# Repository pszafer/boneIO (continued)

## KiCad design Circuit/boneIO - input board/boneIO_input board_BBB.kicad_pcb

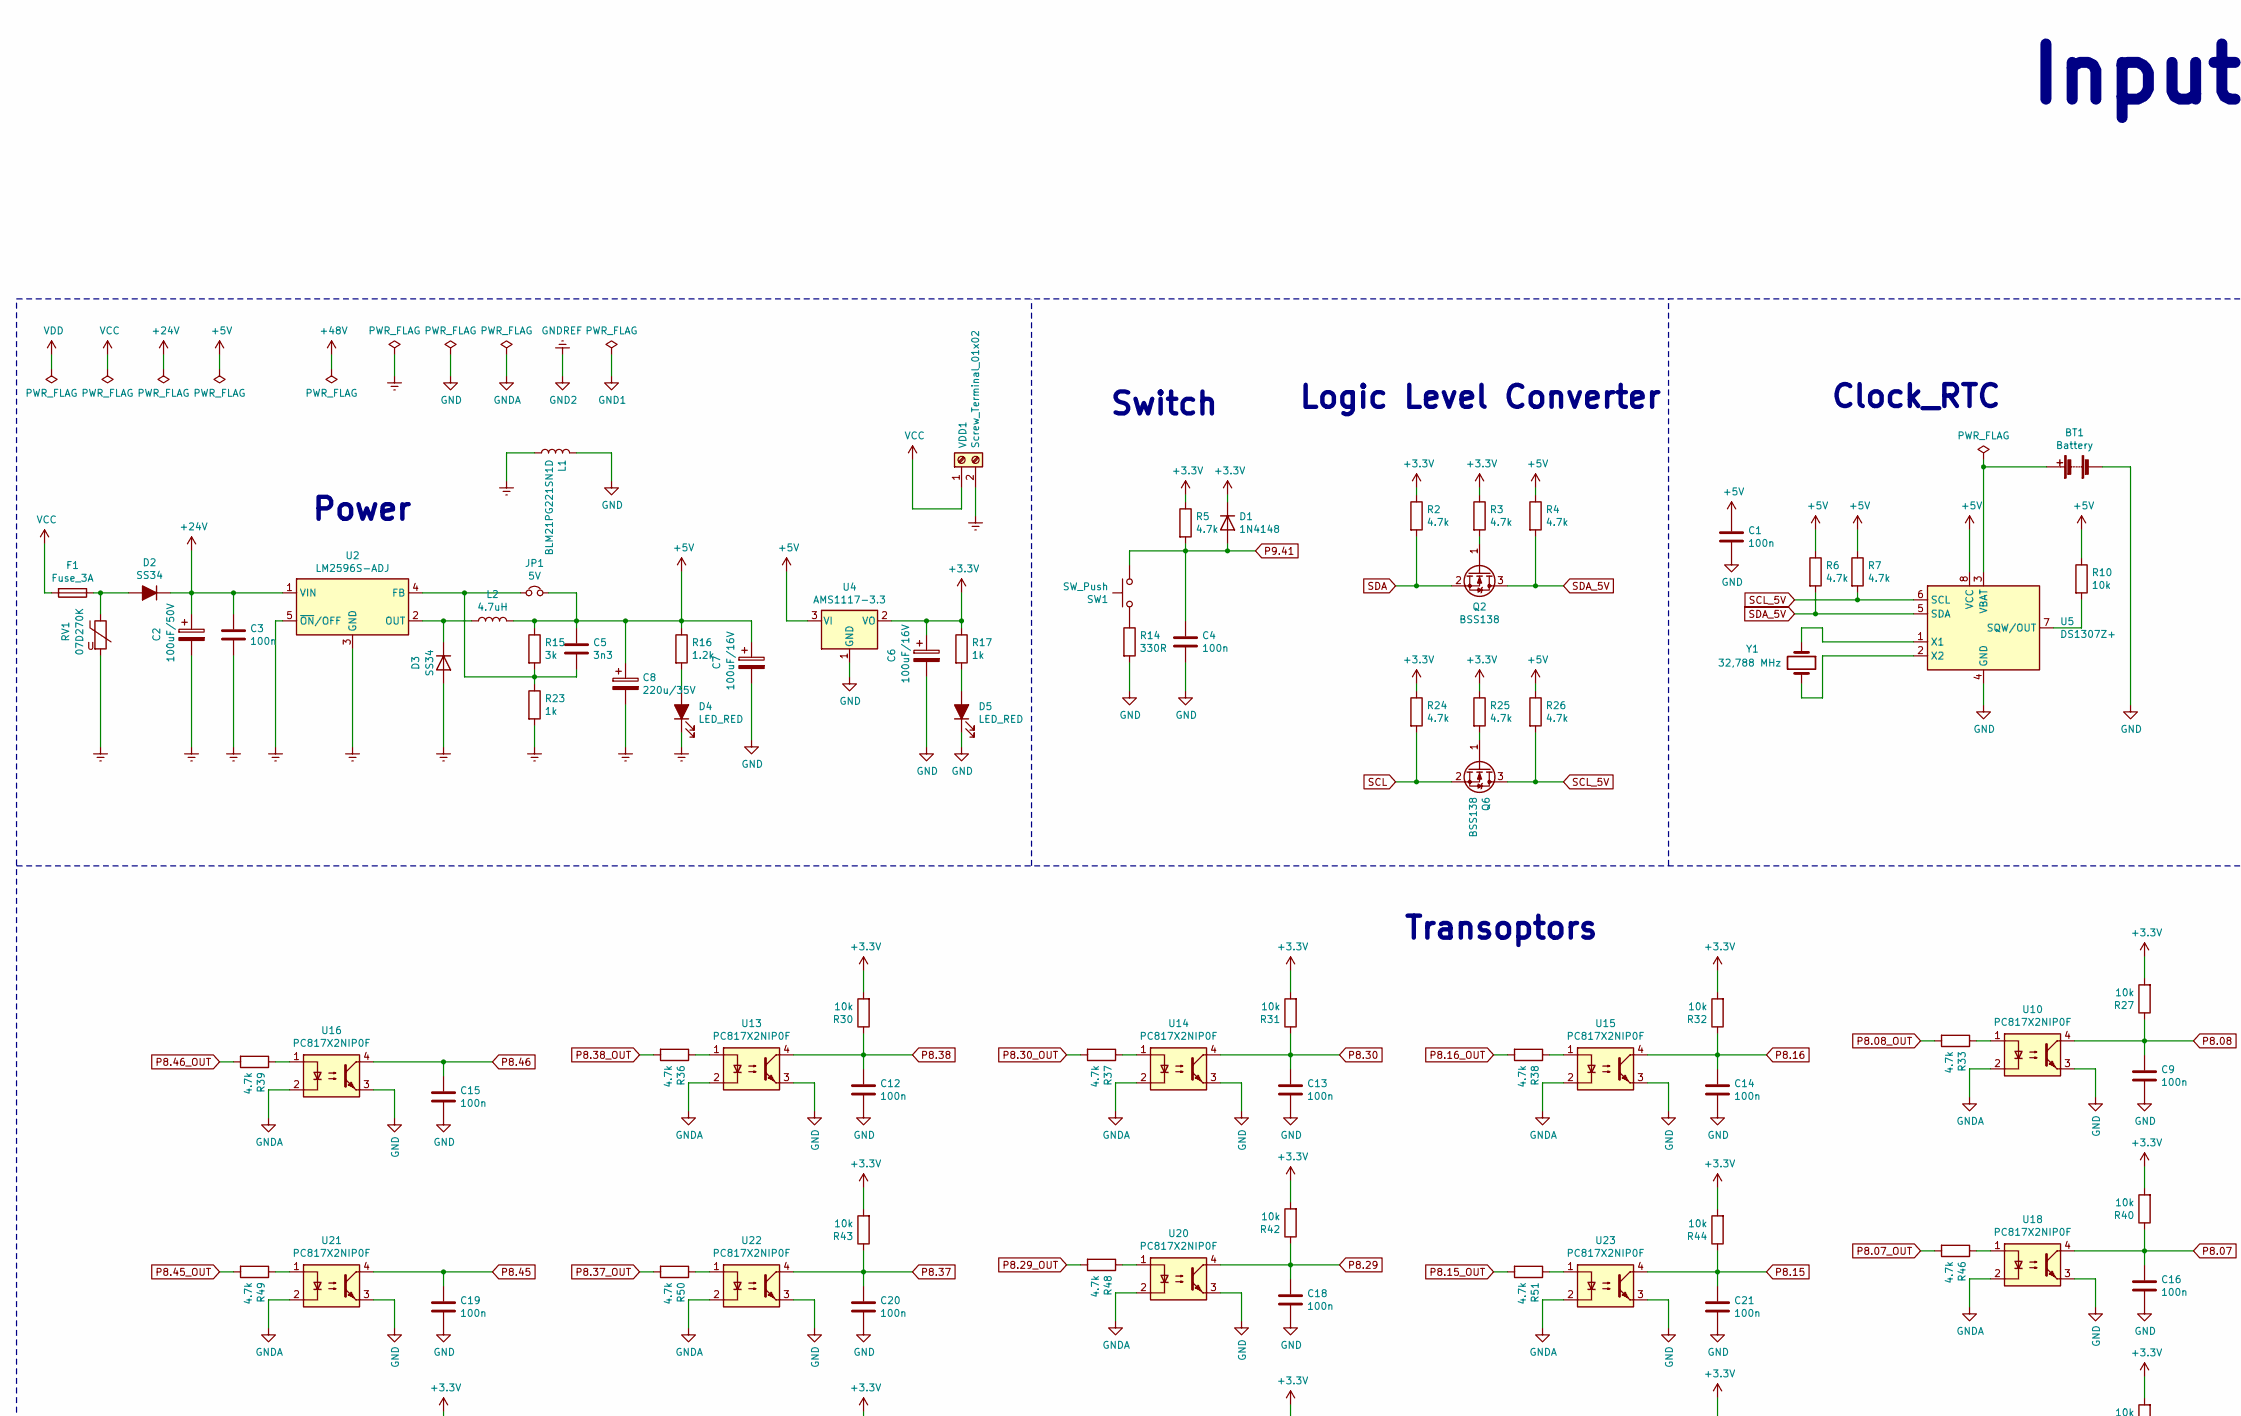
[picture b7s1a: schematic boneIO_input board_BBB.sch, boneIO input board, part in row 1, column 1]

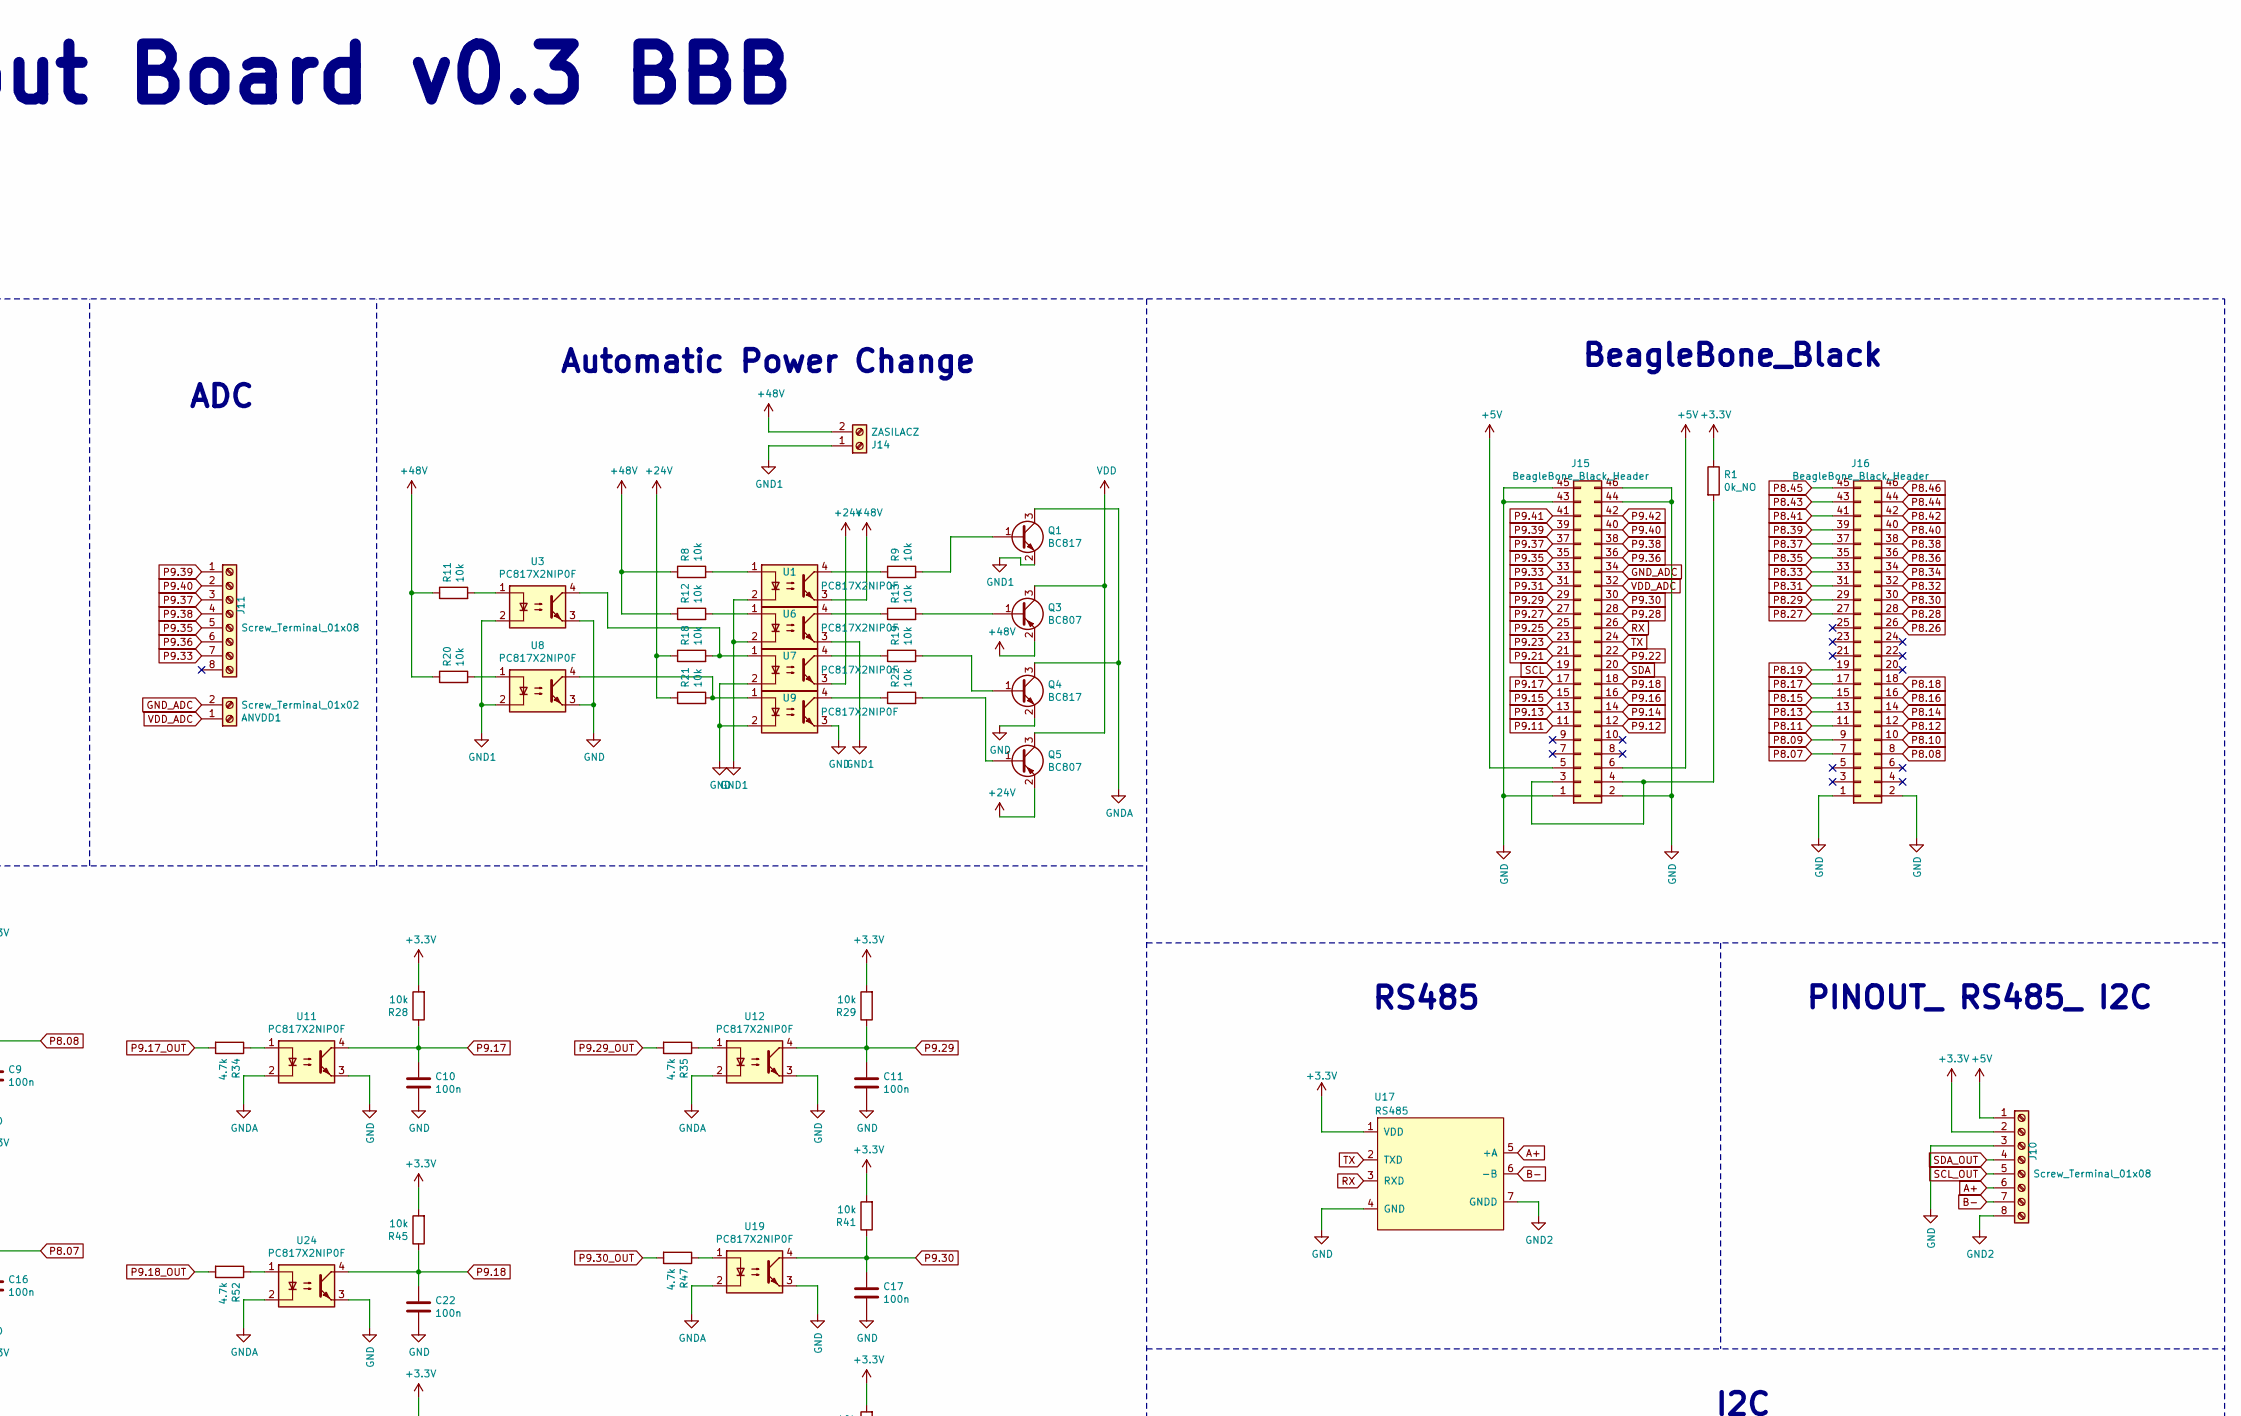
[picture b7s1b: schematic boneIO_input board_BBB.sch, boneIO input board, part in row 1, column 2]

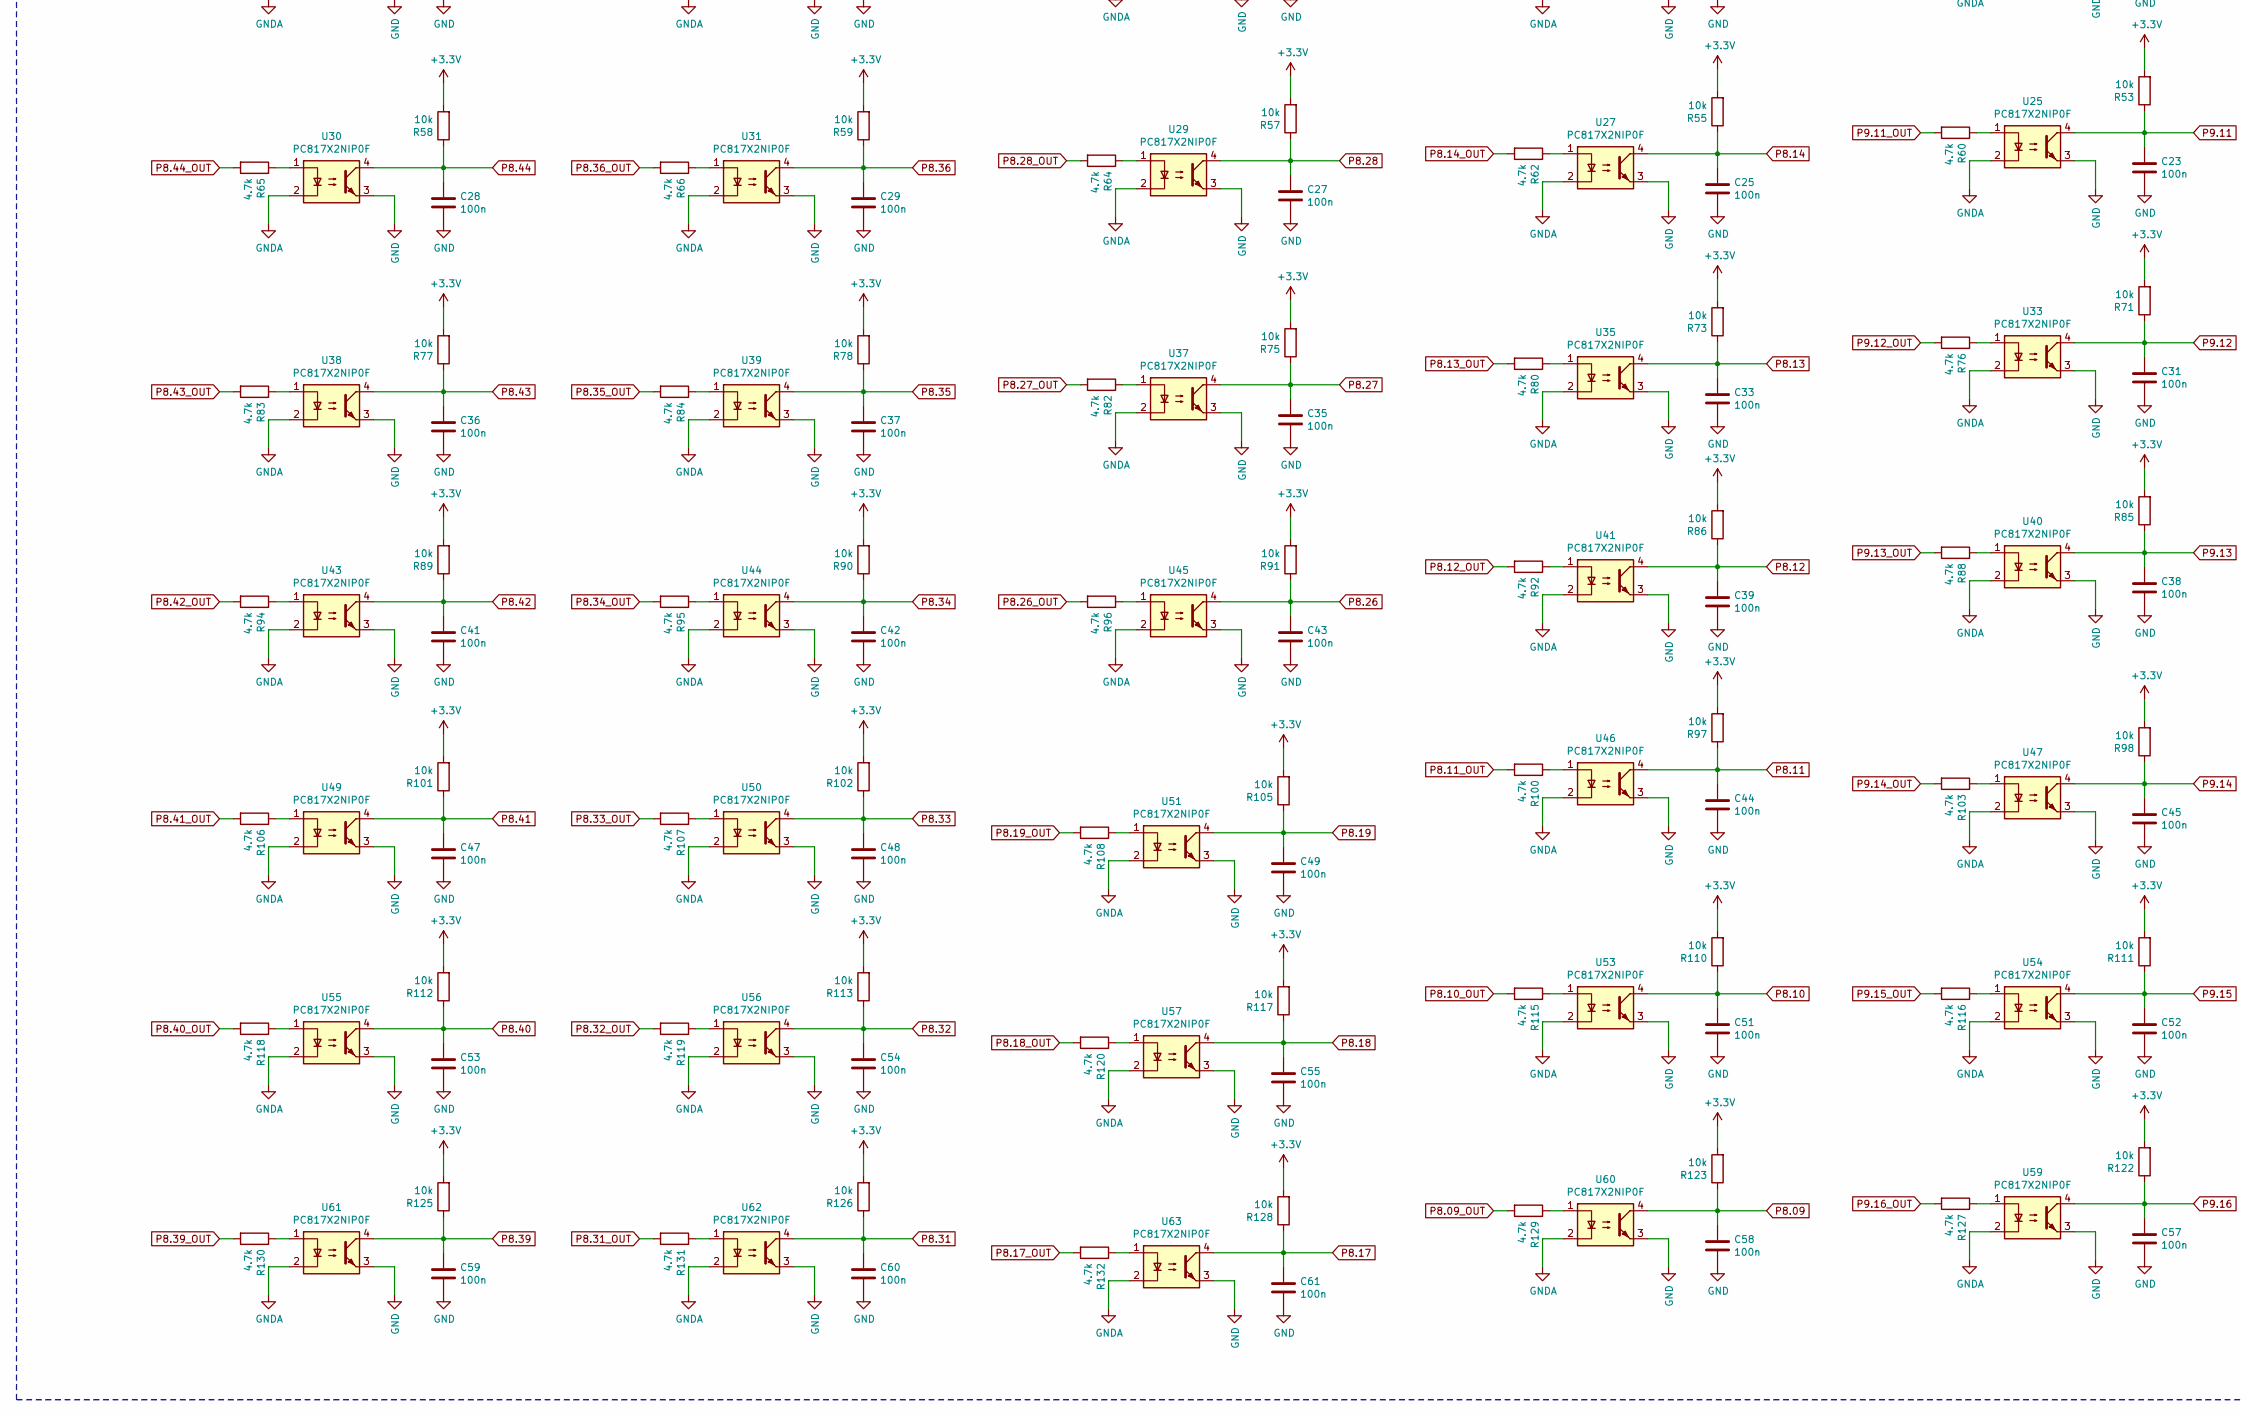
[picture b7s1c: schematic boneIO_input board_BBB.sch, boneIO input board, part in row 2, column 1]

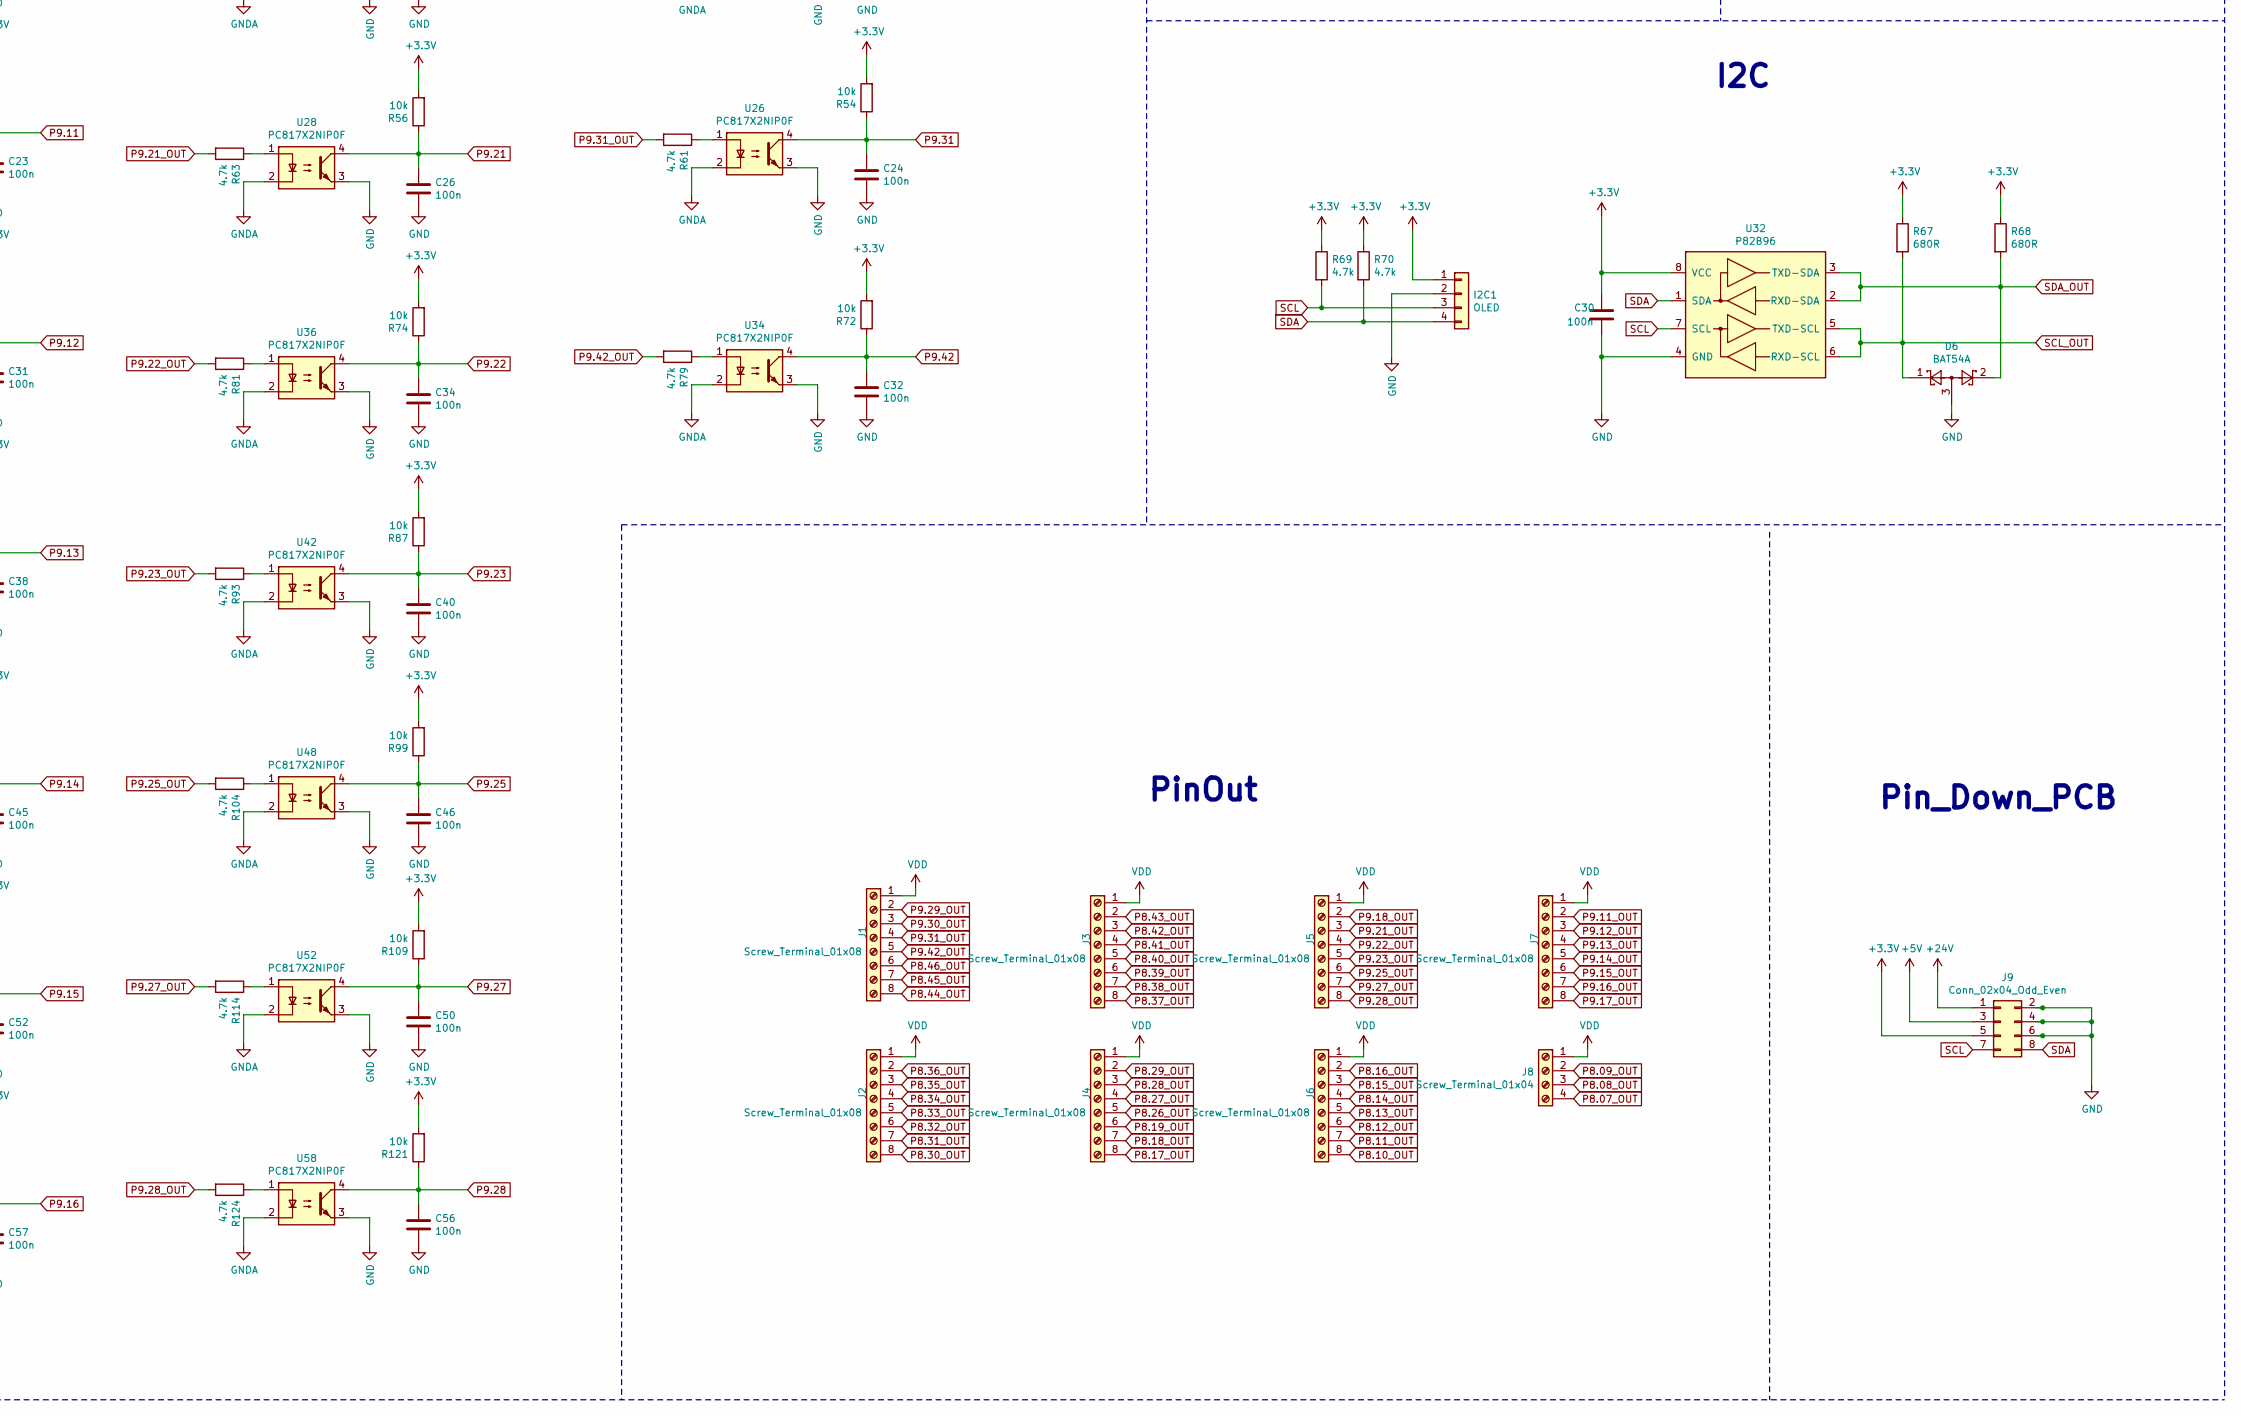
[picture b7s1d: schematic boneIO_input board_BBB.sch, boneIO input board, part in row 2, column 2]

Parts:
ANVDD1: Screw_Terminal_01x02; Phoenix_1x02_P5.00mm_Horizontal
BT1: Battery; Battery_Panasonic_CR1220-VCN_Vertical_CircularHoles
C1, C3, C4, C9, C10, C11, C12, C13, C14, C15, C16, C17, C18, C19, C20, C21, C22, C23, C24, C25, C26, C27, C28, C29, C30, C31, C32, C33, C34, C35, C36, C37, C38, C39, C40, C41, C42, C43, C44, C45, C46, C47, C48, C49, C50, C51, C52, C53, C54, C55, C56, C57, C58, C59, C60, C61: 100n; C_0603_1608Metric; JLCPCB C14663
C2: 100uF/50V; CP_Elec_8x10; JLCPCB C72480
C5: 3n3; C_0805_2012Metric; JLCPCB C107149
C6, C7: 100uF/16V; CP_Elec_6.3x5.4; JLCPCB C72480
C8: 220u/35V; CP_Elec_8x10; JLCPCB C311611
D1: 1N4148; D_MiniMELF; JLCPCB C68883
D2: SS34; D_SMA; JLCPCB C64982
D3: SS34; D_SMA; JLCPCB C8678
D4, D5: LED_RED; LED_0805_2012Metric; JLCPCB C84256
D6: BAT54A; SOT-23
F1: Fuse_3A; Fuse_2512_6332Metric; JLCPCB C136367
I2C1: OLED; PinSocket_1x04_P2.54mm_Vertical
J1, J2, J3, J4, J5, J6, J7, J10, J11: Screw_Terminal_01x08; 8pin
J8: Screw_Terminal_01x04; Phoenix_1x04_P5.00mm_Horizontal
J9: Conn_02x04_Odd_Even; PinSocket_2x04_P2.54mm_Vertical
J14: ZASILACZ; PhoenixContact_MSTBA_2,5_2-G_1x02_P5.00mm_Horizontal
J15, J16: BeagleBone_Black_Header; PinHeader_2x23_P2.54mm_Vertical
JP1: 5V; SolderJumper-2_P1.3mm_Open_Pad1.0x1.5mm
L1: BLM21PG221SN1D; L_0805_2012Metric; JLCPCB C85840
L2: 4.7uH; L_12x12mm_H6mm; JLCPCB C338848
Q1, Q4: BC817; SOT-23
Q2, Q6: BSS138; SOT-23
Q3, Q5: BC807; SOT-23
R1: 0k_NO; R_0805_2012Metric; JLCPCB C238881
R2, R3, R4, R6, R7, R24, R25, R26: 4.7k; R_0603_1608Metric; JLCPCB C238881
R5, R33, R34, R35, R36, R37, R38, R39, R46, R47, R48, R49, R50, R51, R52, R60, R61, R62, R63, R64, R65, R66, R69, R70, R76, R79, R80, R81, R82, R83, R84, R88, R92, R93, R94, R95, R96, R100, R103, R104, R106, R107, R108, R114, R115, R116, R118, R119, R120, R124, R127, R129, R130, R131, R132: 4.7k; R_0603_1608Metric; JLCPCB C237118
R8, R9, R10, R11, R12, R13, R18, R19, R20, R21, R22, R27, R28, R29, R30, R31, R32, R40, R41, R42, R43, R44, R45, R53, R54, R55, R56, R57, R58, R59, R71, R72, R73, R74, R75, R77, R78, R85, R86, R87, R89, R90, R91, R97, R98, R99, R101, R102, R105, R109, R110, R111, R112, R113, R117, R121, R122, R123, R125, R126, R128: 10k; R_0603_1608Metric; JLCPCB C238881
R14: 330R; R_0603_1608Metric; JLCPCB C101062
R15: 3k; R_0603_1608Metric; JLCPCB C126358
R16: 1.2k; R_0603_1608Metric; JLCPCB C269704
R17, R23: 1k; R_0603_1608Metric; JLCPCB C269704
R67, R68: 680R; R_0603_1608Metric; JLCPCB C269704
RV1: 07D270K; RV_Disc_D7mm_W3.5mm_P5mm; JLCPCB C317745
SW1: SW_Push; SW_PUSH_6mm_H13mm
U1, U3, U6, U7, U8, U9, U10, U11, U12, U13, U14, U15, U16, U18, U19, U20, U21, U22, U23, U24, U25, U26, U27, U28, U29, U30, U31, U33, U34, U35, U36, U37, U38, U39, U40, U41, U42, U43, U44, U45, U46, U47, U48, U49, U50, U51, U52, U53, U54, U55, U56, U57, U58, U59, U60, U61, U62, U63: PC817X2NIP0F; SOT254P975X400-4N; JLCPCB C6649
U2: LM2596S-ADJ; TO-263-5_TabPin3
U4: AMS1117-3.3; SOT-223-3_TabPin2
U5: DS1307Z+; SOIC-8_3.9x4.9mm_P1.27mm; JLCPCB C26858
U17: RS485; RS485_moduleTTL
U32: P82B96; SO-8_3.9x4.9mm_P1.27mm; JLCPCB C32103
VDD1: Screw_Terminal_01x02; Phoenix_1x02_P5.00mm_Horizontal
Y1: 32,788 MHz; Crystal_C26-LF_D2.1mm_L6.5mm_Horizontal

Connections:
+3V3: C6.1, C30.1, D1.1 (K), I2C1.1, J9.5, J10.2, R1.1, R2.1, R3.1, R5.1, R17.1, R24.1, R25.1, R27.2, R28.2, R29.2, R30.2, R31.2, R32.2, R40.2, R41.2, R42.2, R43.2, R44.2, R45.2, R53.2, R54.2, R55.2, R56.2, R57.2, R58.2, R59.2, R67.1, R68.1, R69.1, R70.1, R71.2, R72.2, R73.2, R74.2, R75.2, R77.2, R78.2, R85.2, R86.2, R87.2, R89.2, R90.2, R91.2, R97.2, R98.2, R99.2, R101.2, R102.2, R105.2, R109.2, R110.2, R111.2, R112.2, R113.2, R117.2, R121.2, R122.2, R123.2, R125.2, R126.2, R128.2, U4.2 (VO), U17.1 (VDD), U32.8 (VCC)
+5V: C1.1, C5.1, C7.1, C8.1, J9.3, J10.1, J15.5, J15.6, JP1.2, L2.2, R4.1, R6.1, R7.1, R10.1, R15.1, R16.1, R26.1, U4.3 (VI), U5.8 (VCC)
+24V: C2.1, C3.1, D2.1 (K), J9.1, Q5.2 (E), R18.1, R21.1, U2.1 (VIN), U7.3
+48V: J14.2, Q3.2 (E), R8.1, R11.1, R12.1, R20.1, U1.3
A+: J10.6, U17.5 (+A)
B-: J10.7, U17.6 (-B)
Earth: C2.2, C3.2, C8.2, D3.2 (A), D4.1 (K), L1.1, R23.2, RV1.2, U2.3 (GND), U2.5 (~ON~/OFF), VDD1.2
GND: BT1.2 (-), C1.2, C4.2, C6.2, C7.2, C9.2, C10.2, C11.2, C12.2, C13.2, C14.2, C15.2, C16.2, C17.2, C18.2, C19.2, C20.2, C21.2, C22.2, C23.2, C24.2, C25.2, C26.2, C27.2, C28.2, C29.2, C30.2, C31.2, C32.2, C33.2, C34.2, C35.2, C36.2, C37.2, C38.2, C39.2, C40.2, C41.2, C42.2, C43.2, C44.2, C45.2, C46.2, C47.2, C48.2, C49.2, C50.2, C51.2, C52.2, C53.2, C54.2, C55.2, C56.2, C57.2, C58.2, C59.2, C60.2, C61.2, D5.1 (K), D6.3, I2C1.2, J9.2, J9.4, J9.6, J10.3, J15.1, J15.2, J15.43, J15.44, J15.45, J15.46, J16.1, J16.2, L1.2, Q4.2 (E), R14.2, U3.3, U4.1 (GND), U5.4 (GND), U7.2, U8.3, U9.2, U9.3, U10.3, U11.3, U12.3, U13.3, U14.3, U15.3, U16.3, U17.4 (GND), U18.3, U19.3, U20.3, U21.3, U22.3, U23.3, U24.3, U25.3, U26.3, U27.3, U28.3, U29.3, U30.3, U31.3, U32.4 (GND), U33.3, U34.3, U35.3, U36.3, U37.3, U38.3, U39.3, U40.3, U41.3, U42.3, U43.3, U44.3, U45.3, U46.3, U47.3, U48.3, U49.3, U50.3, U51.3, U52.3, U53.3, U54.3, U55.3, U56.3, U57.3, U58.3, U59.3, U60.3, U61.3, U62.3, U63.3
GND1: J14.1, Q1.2 (E), U1.2, U3.2, U6.2, U6.3, U8.2
GND2: J10.8, U17.7 (GNDD)
GNDA: Q1.3 (C), Q4.3 (C), U10.2, U11.2, U12.2, U13.2, U14.2, U15.2, U16.2, U18.2, U19.2, U20.2, U21.2, U22.2, U23.2, U24.2, U25.2, U26.2, U27.2, U28.2, U29.2, U30.2, U31.2, U33.2, U34.2, U35.2, U36.2, U37.2, U38.2, U39.2, U40.2, U41.2, U42.2, U43.2, U44.2, U45.2, U46.2, U47.2, U48.2, U49.2, U50.2, U51.2, U52.2, U53.2, U54.2, U55.2, U56.2, U57.2, U58.2, U59.2, U60.2, U61.2, U62.2, U63.2
GND_ADC: ANVDD1.2, J15.34
unnamed: BT1.1 (+), U5.3 (VBAT)
unnamed: C5.2, JP1.1, R15.2, R23.1, U2.4 (FB)
unnamed: D2.2 (A), F1.1, RV1.1
unnamed: D3.1 (K), L2.1, U2.2 (OUT)
unnamed: D4.2 (A), R16.2
unnamed: D5.2 (A), R17.2
unnamed: J15.3, J15.4, R1.2
unnamed: Q1.1 (B), R9.2
unnamed: Q2.1 (G), R3.2
unnamed: Q3.1 (B), R13.2
unnamed: Q4.1 (B), R19.2
unnamed: Q5.1 (B), R22.2
unnamed: Q6.1 (G), R25.2
unnamed: R8.2, U1.1
unnamed: R9.1, U1.4
unnamed: R10.2, U5.7 (SQW/OUT)
unnamed: R11.2, U3.1
unnamed: R12.2, U6.1
unnamed: R13.1, U6.4
unnamed: R14.1, SW1.1
unnamed: R18.2, U3.4, U7.1
unnamed: R19.1, U7.4
unnamed: R20.2, U8.1
unnamed: R21.2, U8.4, U9.1
unnamed: R22.1, U9.4
unnamed: R33.1, U10.1
unnamed: R34.1, U11.1
unnamed: R35.1, U12.1
unnamed: R36.1, U13.1
unnamed: R37.1, U14.1
unnamed: R38.1, U15.1
unnamed: R39.1, U16.1
unnamed: R46.1, U18.1
unnamed: R47.1, U19.1
unnamed: R48.1, U20.1
unnamed: R49.1, U21.1
unnamed: R50.1, U22.1
unnamed: R51.1, U23.1
unnamed: R52.1, U24.1
unnamed: R60.1, U25.1
unnamed: R61.1, U26.1
unnamed: R62.1, U27.1
unnamed: R63.1, U28.1
unnamed: R64.1, U29.1
unnamed: R65.1, U30.1
unnamed: R66.1, U31.1
unnamed: R76.1, U33.1
unnamed: R79.1, U34.1
unnamed: R80.1, U35.1
unnamed: R81.1, U36.1
unnamed: R82.1, U37.1
unnamed: R83.1, U38.1
unnamed: R84.1, U39.1
unnamed: R88.1, U40.1
unnamed: R92.1, U41.1
unnamed: R93.1, U42.1
unnamed: R94.1, U43.1
unnamed: R95.1, U44.1
unnamed: R96.1, U45.1
unnamed: R100.1, U46.1
unnamed: R103.1, U47.1
unnamed: R104.1, U48.1
unnamed: R106.1, U49.1
unnamed: R107.1, U50.1
unnamed: R108.1, U51.1
unnamed: R114.1, U52.1
unnamed: R115.1, U53.1
unnamed: R116.1, U54.1
unnamed: R118.1, U55.1
unnamed: R119.1, U56.1
unnamed: R120.1, U57.1
unnamed: R124.1, U58.1
unnamed: R127.1, U59.1
unnamed: R129.1, U60.1
unnamed: R130.1, U61.1
unnamed: R131.1, U62.1
unnamed: R132.1, U63.1
unnamed: U5.1 (X1), Y1.1
unnamed: U5.2 (X2), Y1.2
P8.07: C16.1, J16.7, R40.1, U18.4
P8.07_OUT: J8.4, R46.2
P8.08: C9.1, J16.8, R27.1, U10.4
P8.08_OUT: J8.3, R33.2
P8.09: C58.1, J16.9, R123.1, U60.4
P8.09_OUT: J8.2, R129.2
P8.10: C51.1, J16.10, R110.1, U53.4
P8.10_OUT: J6.8, R115.2
P8.11: C44.1, J16.11, R97.1, U46.4
P8.11_OUT: J6.7, R100.2
P8.12: C39.1, J16.12, R86.1, U41.4
P8.12_OUT: J6.6, R92.2
P8.13: C33.1, J16.13, R73.1, U35.4
P8.13_OUT: J6.5, R80.2
P8.14: C25.1, J16.14, R55.1, U27.4
P8.14_OUT: J6.4, R62.2
P8.15: C21.1, J16.15, R44.1, U23.4
P8.15_OUT: J6.3, R51.2
P8.16: C14.1, J16.16, R32.1, U15.4
P8.16_OUT: J6.2, R38.2
P8.17: C61.1, J16.17, R128.1, U63.4
P8.17_OUT: J4.8, R132.2
P8.18: C55.1, J16.18, R117.1, U57.4
P8.18_OUT: J4.7, R120.2
P8.19: C49.1, J16.19, R105.1, U51.4
P8.19_OUT: J4.6, R108.2
P8.26: C43.1, J16.26, R91.1, U45.4
P8.26_OUT: J4.5, R96.2
P8.27: C35.1, J16.27, R75.1, U37.4
P8.27_OUT: J4.4, R82.2
P8.28: C27.1, J16.28, R57.1, U29.4
P8.28_OUT: J4.3, R64.2
P8.29: C18.1, J16.29, R42.1, U20.4
P8.29_OUT: J4.2, R48.2
P8.30: C13.1, J16.30, R31.1, U14.4
P8.30_OUT: J2.8, R37.2
P8.31: C60.1, J16.31, R126.1, U62.4
P8.31_OUT: J2.7, R131.2
P8.32: C54.1, J16.32, R113.1, U56.4
P8.32_OUT: J2.6, R119.2
P8.33: C48.1, J16.33, R102.1, U50.4
P8.33_OUT: J2.5, R107.2
P8.34: C42.1, J16.34, R90.1, U44.4
P8.34_OUT: J2.4, R95.2
P8.35: C37.1, J16.35, R78.1, U39.4
P8.35_OUT: J2.3, R84.2
P8.36: C29.1, J16.36, R59.1, U31.4
P8.36_OUT: J2.2, R66.2
P8.37: C20.1, J16.37, R43.1, U22.4
P8.37_OUT: J3.8, R50.2
P8.38: C12.1, J16.38, R30.1, U13.4
P8.38_OUT: J3.7, R36.2
P8.39: C59.1, J16.39, R125.1, U61.4
P8.39_OUT: J3.6, R130.2
P8.40: C53.1, J16.40, R112.1, U55.4
P8.40_OUT: J3.5, R118.2
P8.41: C47.1, J16.41, R101.1, U49.4
P8.41_OUT: J3.4, R106.2
P8.42: C41.1, J16.42, R89.1, U43.4
P8.42_OUT: J3.3, R94.2
P8.43: C36.1, J16.43, R77.1, U38.4
P8.43_OUT: J3.2, R83.2
P8.44: C28.1, J16.44, R58.1, U30.4
P8.44_OUT: J1.8, R65.2
P8.45: C19.1, J16.45, U21.4
P8.45_OUT: J1.7, R49.2
P8.46: C15.1, J16.46, U16.4
P8.46_OUT: J1.6, R39.2
P9.11: C23.1, J15.11, R53.1, U25.4
P9.11_OUT: J7.2, R60.2
P9.12: C31.1, J15.12, R71.1, U33.4
P9.12_OUT: J7.3, R76.2
P9.13: C38.1, J15.13, R85.1, U40.4
P9.13_OUT: J7.4, R88.2
P9.14: C45.1, J15.14, R98.1, U47.4
P9.14_OUT: J7.5, R103.2
P9.15: C52.1, J15.15, R111.1, U54.4
P9.15_OUT: J7.6, R116.2
P9.16: C57.1, J15.16, R122.1, U59.4
P9.16_OUT: J7.7, R127.2
P9.17: C10.1, J15.17, R28.1, U11.4
P9.17_OUT: J7.8, R34.2
P9.18: C22.1, J15.18, R45.1, U24.4
P9.18_OUT: J5.2, R52.2
P9.21: C26.1, J15.21, R56.1, U28.4
P9.21_OUT: J5.3, R63.2
P9.22: C34.1, J15.22, R74.1, U36.4
P9.22_OUT: J5.4, R81.2
P9.23: C40.1, J15.23, R87.1, U42.4
P9.23_OUT: J5.5, R93.2
P9.25: C46.1, J15.25, R99.1, U48.4
P9.25_OUT: J5.6, R104.2
P9.27: C50.1, J15.27, R109.1, U52.4
P9.27_OUT: J5.7, R114.2
P9.28: C56.1, J15.28, R121.1, U58.4
P9.28_OUT: J5.8, R124.2
P9.29: C11.1, J15.29, R29.1, U12.4
P9.29_OUT: J1.2, R35.2
P9.30: C17.1, J15.30, R41.1, U19.4
P9.30_OUT: J1.3, R47.2
P9.31: C24.1, J15.31, R54.1, U26.4
P9.31_OUT: J1.4, R61.2
P9.33: J11.7, J15.33
P9.35: J11.5, J15.35
P9.36: J11.6, J15.36
P9.37: J11.3, J15.37
P9.38: J11.4, J15.38
P9.39: J11.1, J15.39
P9.40: J11.2, J15.40
P9.41: C4.1, D1.2 (A), J15.41, R5.2, SW1.2
P9.42: C32.1, J15.42, R72.1, U34.4
P9.42_OUT: J1.5, R79.2
RX: J15.26, U17.3 (RXD)
SCL: I2C1.3, J9.7, J15.19, Q6.2 (S), R24.2, R69.2, U32.7 (SCL)
SCL_5V: Q6.3 (D), R7.2, R26.2, U5.6 (SCL)
SCL_OUT: D6.1, J10.5, R67.2, U32.5 (TXD-SCL), U32.6 (RXD-SCL)
SDA: I2C1.4, J9.8, J15.20, Q2.2 (S), R2.2, R70.2, U32.1 (SDA)
SDA_5V: Q2.3 (D), R4.2, R6.2, U5.5 (SDA)
SDA_OUT: D6.2, J10.4, R68.2, U32.2 (RXD-SDA), U32.3 (TXD-SDA)
TX: J15.24, U17.2 (TXD)
VCC: F1.2, VDD1.1
VDD: J1.1, J2.1, J3.1, J4.1, J5.1, J6.1, J7.1, J8.1, Q3.3 (C), Q5.3 (C)
VDD_ADC: ANVDD1.1, J15.32

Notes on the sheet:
Power
I2C
Switch
BeagleBone_Black
RS485
PinOut
Transoptors
ADC
PINOUT_ RS485_ I2C
Pin_Down_PCB
Automatic Power Change
Input Board v0.3 BBB
Clock_RTC
Logic Level Converter

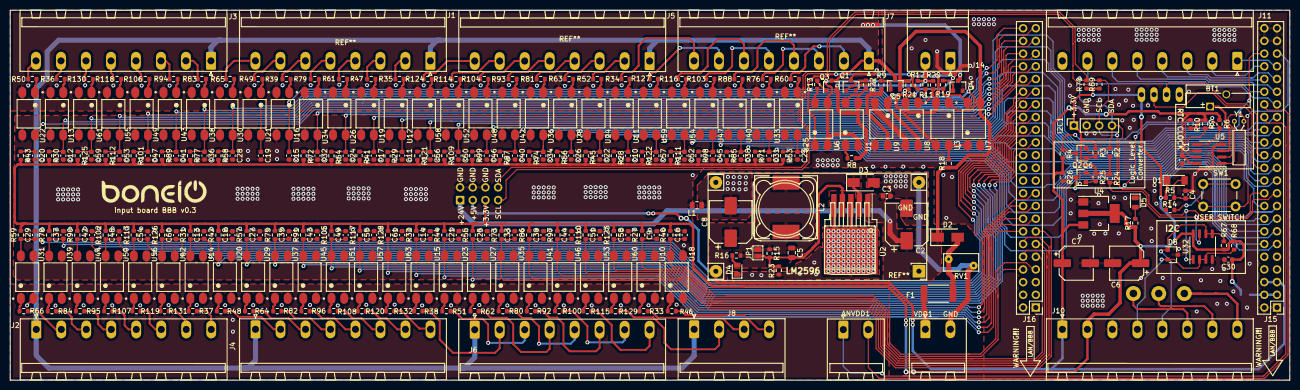
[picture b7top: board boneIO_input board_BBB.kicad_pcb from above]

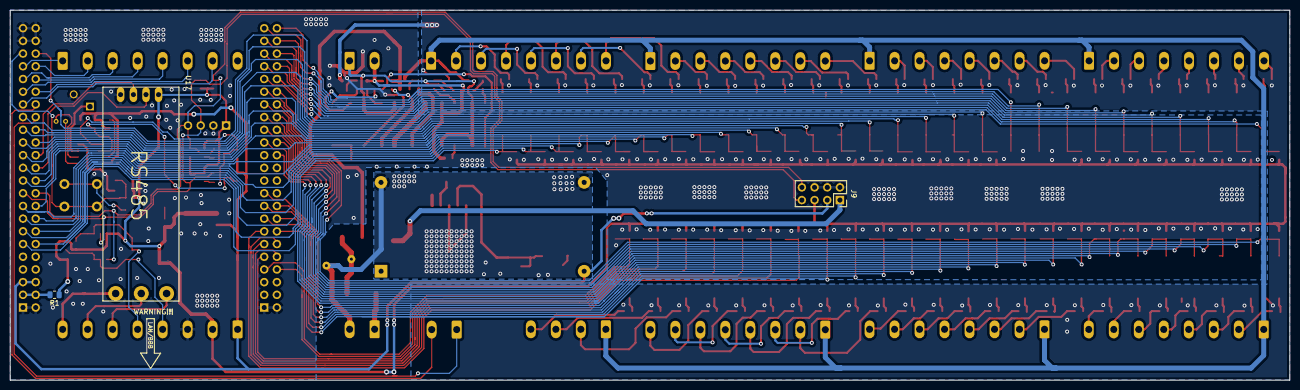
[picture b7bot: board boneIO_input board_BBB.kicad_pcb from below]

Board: 2 copper layers, 256.0 x 74.0 mm, 293 parts (3 on the bottom side), 214 nets.

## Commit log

2021-11-15 Poprawiono gold piny, dodano .stp przekładek między płytkami
2021-11-18 Correction of a schematic error and repair of 3d models
2021-11-18 switch to YAML config
2021-11-19 correcting the scheme
2021-11-19 cleaning folders
2021-11-24 24x16 cleanup
2021-11-25 Relay model fixed
2021-11-29 fix gpio kind choose
2021-12-04 24x16 v0.3
2021-12-04 32x5 v0.3
2021-12-04 relay board v0.3 and some cleanup
2021-12-04 added photo of v0.2
2021-12-04 added new photos of v0.2
2021-12-04 added photos to readme
2021-12-05 add support for YAML config, YAML include, I2C, MCP23017, OLED display, stats display.
2021-12-06 rename bone to boneio, add support for oled
2021-12-07 Minor fixes, v0.3 electronic assembly in step file, stl files for all parts
2021-12-07 add OLED callbacks handler, sort imports
2021-12-07 fix version displaying in mqtt
2021-12-07 add handling spaces in output id
2021-12-07 add ha discovery for inputs
2021-12-07 add LM75 sensor
2021-12-07 refresh example config
2021-12-07 fix sensor module
2021-12-07 Create 1
2021-12-08 add exception handling, fix no sensor,oled configured.
2021-12-08 remove debug flag in service
2021-12-08 fix examples
2021-12-09 add gpio as sensor pressed,released
2021-12-09 Add files via upload
    Poprawione
2021-12-10 ADC support, more examples
2021-12-10 add adc schema
2021-12-11 Some minor fixes
    - added external voltage regulator for 3.3V
    - changed names of connectors to be the same as in v0.2
2021-12-11 Add files via upload
    Poprawione według wskazówek. Wszystkie elementy z jednej strony. Wzmocnione ścieżki HV. Poprawiona numeracja płyty.
2021-12-11 Added vents on top and bottom and some other minor improvements
2021-12-12 initialize inputs
2021-12-12 oled tolerance for network fault
2021-12-12 Add files via upload
    Przesunięte triaki i warystory.
2021-12-13 Add files via upload
    Jumpery po stronie bottom.
2021-12-13 add unique queue implementation
2021-12-13 send empty payload for input
2021-12-14 new pcb 24x10A
2021-12-18 update input_board_BBB v0.3
    update input_board_BBB v0.3
2021-12-18 corrected version
2021-12-18 corrected numbering
2021-12-18 removal of gerberas
2021-12-18 corrected J14
2021-12-18 Removed folder without BBB suffix
2021-12-18 Changed place of K labels
2021-12-19 Moved some labels
2021-12-19 boneIO - shutter board 32x10A
2021-12-19 Added no connection flags to schema
2021-12-19 Poprawiana wersja
2021-12-19 Automatic PSU Switch v0.2
2021-12-19 reduced PCB
2021-12-19 New PCB
2021-12-22 Delete Circuit/boneIO - input board_ESP directory
    Not ready for orders
2021-12-29 boneIO v0.3 final case with electronic assembly
2022-01-17 Moved case, circuit and code into separate repositories
2022-01-17 Added link to new repositories.
2022-02-23 Changed link to documentation.
2022-06-20 add sponsor button
2022-06-20 add 2nd line
